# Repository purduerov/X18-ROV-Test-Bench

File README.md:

# X18 ROV Test Bench

Surface test-bench hardware for the Purdue ROV team (X18 vehicle generation):
carrier and power boards for topside validation without the vehicle in the water.

## Layout

- `MCU and Pi Board/` — MCU + Raspberry Pi carrier board
  (`mcu and pi board.kicad_sch` / `.kicad_pcb`, project-local `Libraries/`,
  `custom library.*`)
- `power/` — power distribution board (`power.kicad_sch` / `.kicad_pcb`,
  `power_symbols.*`, rail sheets such as `12-5`, `48-12`, `STM`)

## Tooling

- Designed in KiCad — open the `.kicad_pro` in each board folder.
- Fab/plot outputs (`outputs/`, `manufacturing/`, Gerbers), KiCad
  auto-backups (`*-backups/`), caches, and component source archives
  (`*.zip`) are git-ignored; regenerate them locally.

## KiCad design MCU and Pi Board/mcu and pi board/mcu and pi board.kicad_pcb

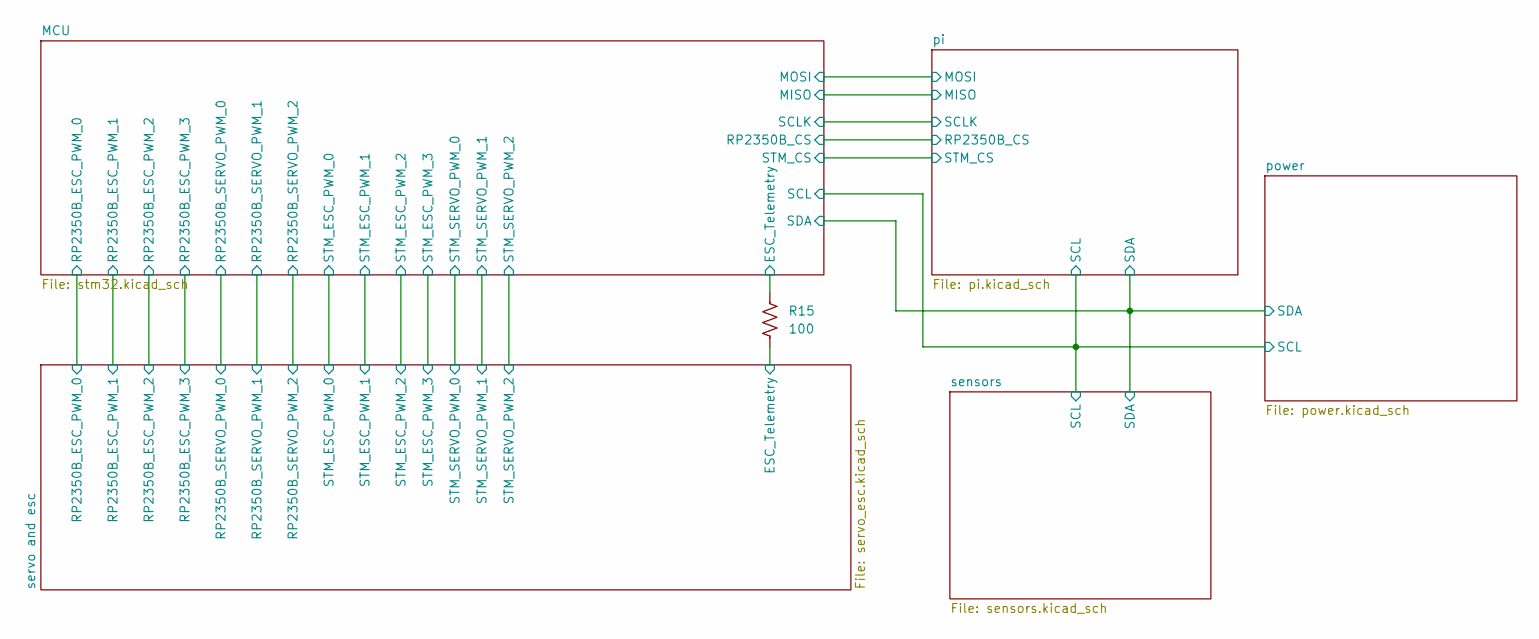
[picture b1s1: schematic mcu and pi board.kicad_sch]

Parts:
R15: 100; R_0603_1608Metric_Pad0.98x0.95mm_HandSolder

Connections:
/MCU/GPIO13: R15.1; also elsewhere on the board
/servo and esc/ESC_Telemetry: R15.2; also elsewhere on the board

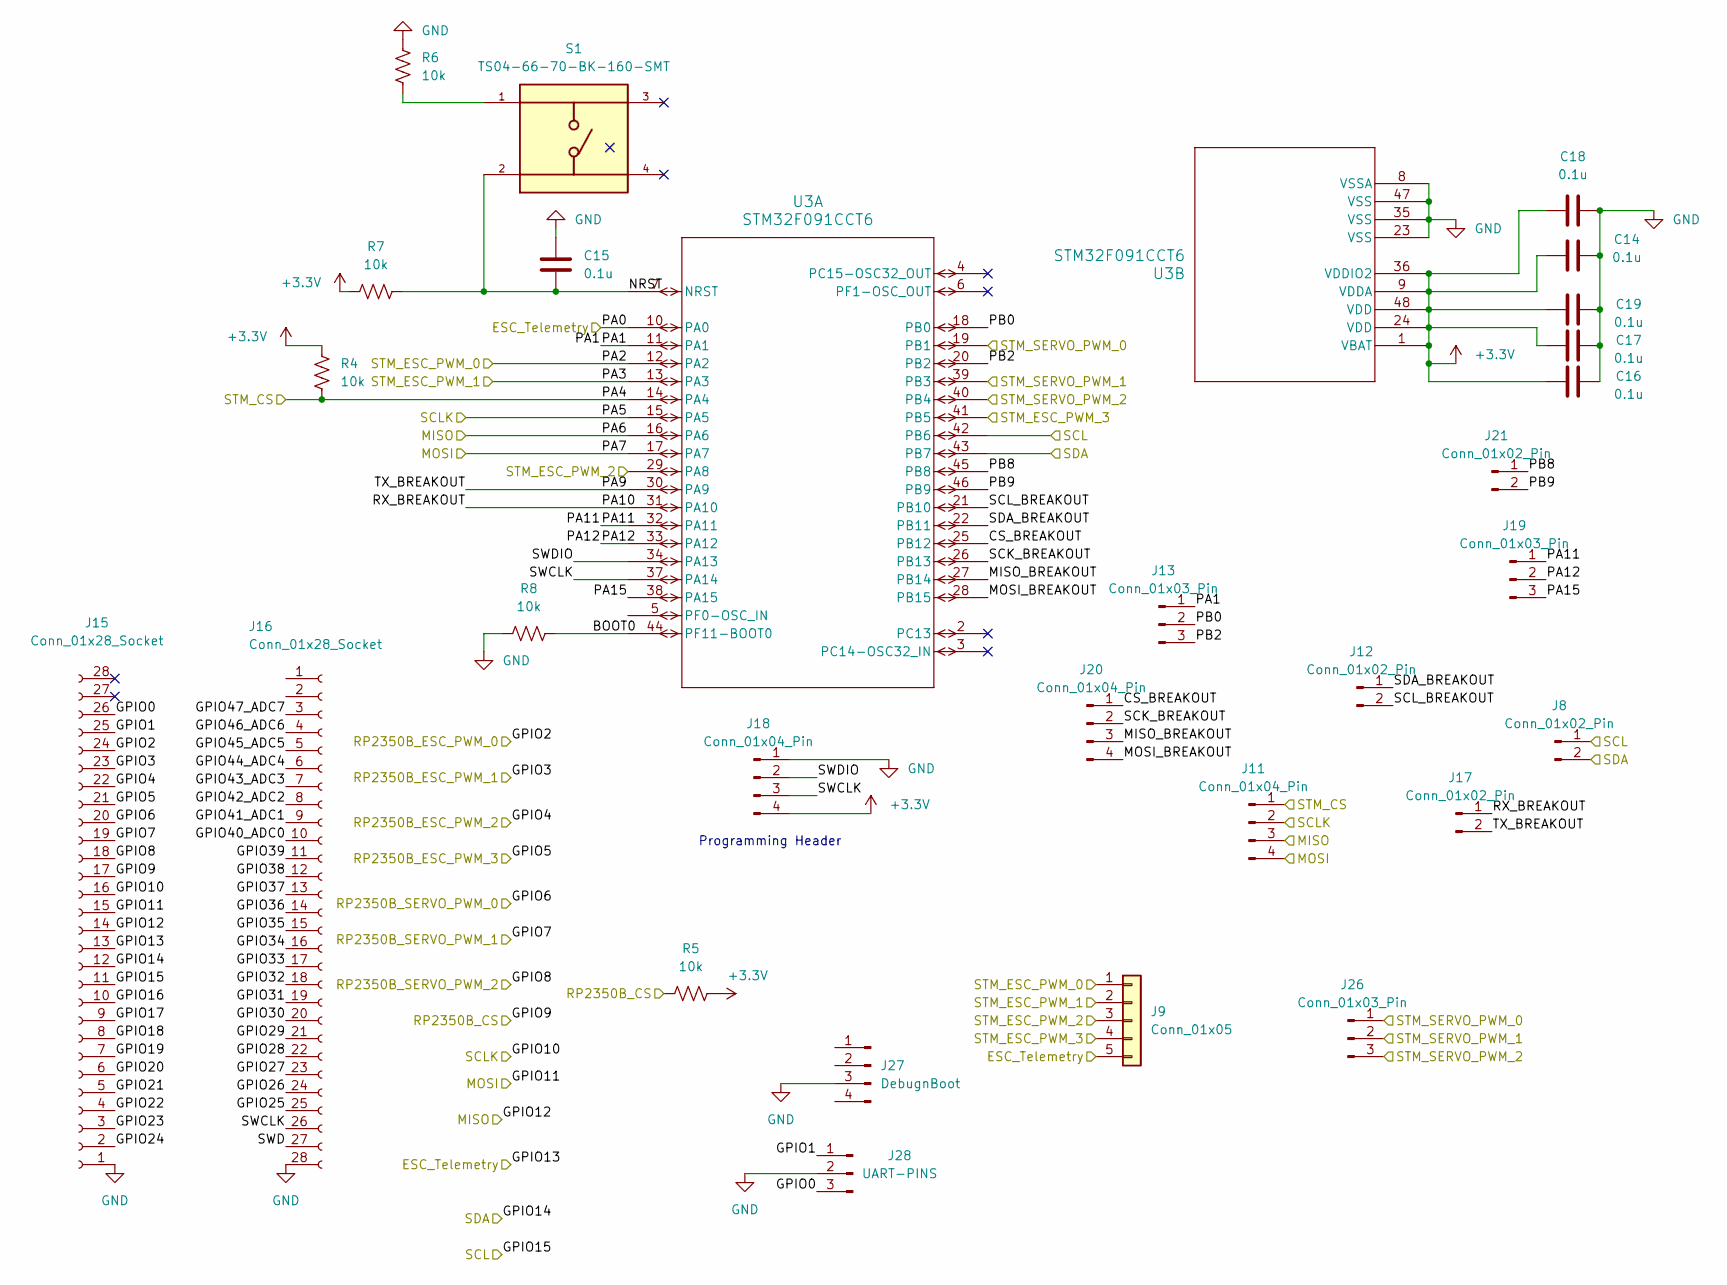
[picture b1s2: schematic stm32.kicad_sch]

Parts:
C14, C15, C16, C17, C18, C19: 0.1u; C_0603_1608Metric_Pad1.08x0.95mm_HandSolder; Voltage Rating 10V
J8, J12, J21: Conn_01x02_Pin; PinHeader_1x02_P2.54mm_Vertical
J9: Conn_01x05; PinSocket_1x05_P2.54mm_Vertical
J11, J18, J20: Conn_01x04_Pin; PinHeader_1x04_P2.54mm_Vertical
J13, J19: Conn_01x03_Pin; PinHeader_1x03_P2.54mm_Vertical
J15, J16: Conn_01x28_Socket; PinSocket_1x28_P2.54mm_Vertical
J17: Conn_01x02_Pin; PinSocket_1x02_P2.54mm_Vertical
J26: Conn_01x03_Pin; PinSocket_1x03_P2.54mm_Vertical
J27: DebugnBoot; PinHeader_1x04_P2.54mm_Vertical
J28: UART-PINS; PinHeader_1x03_P2.54mm_Vertical
R4, R5, R6, R7, R8: 10k; R_0603_1608Metric_Pad0.98x0.95mm_HandSolder
S1: TS04-66-70-BK-160-SMT; SW_TS04-66-70-BK-160-SMT; PARTREV 1.0
U3: STM32F091CCT6; LQFP48-7x7mm

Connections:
+3.3V: C14.1, C16.1, C17.1, C18.1, C19.1, J18.4, R4.1, R5.2, R7.1, U3.1 (VBAT), U3.9 (VDDA), U3.24 (VDD), U3.36 (VDDIO2), U3.48 (VDD); also elsewhere on the board
/MCU/BOOT0: R8.2, U3.44 (PF11-BOOT0)
/MCU/CS_BREAKOUT: J20.1, U3.25 (PB12)
/MCU/GPIO0: J15.26, J28.3
/MCU/GPIO1: J15.25, J28.1
/MCU/GPIO2: J15.24; also elsewhere on the board
/MCU/GPIO3: J15.23; also elsewhere on the board
/MCU/GPIO4: J15.22; also elsewhere on the board
/MCU/GPIO5: J15.21; also elsewhere on the board
/MCU/GPIO6: J15.20; also elsewhere on the board
/MCU/GPIO7: J15.19; also elsewhere on the board
/MCU/GPIO8: J15.18; also elsewhere on the board
/MCU/GPIO9: J15.17, R5.1; also elsewhere on the board
/MCU/GPIO10: J11.2, J15.16, U3.15 (PA5); also elsewhere on the board
/MCU/GPIO11: J11.4, J15.15, U3.17 (PA7); also elsewhere on the board
/MCU/GPIO12: J11.3, J15.14, U3.16 (PA6); also elsewhere on the board
/MCU/GPIO13: J9.5, J15.13, U3.10 (PA0); also elsewhere on the board
/MCU/GPIO14: J8.2, J15.12, U3.43 (PB7); also elsewhere on the board
/MCU/GPIO15: J8.1, J15.11, U3.42 (PB6); also elsewhere on the board
/MCU/GPIO16: J15.10
/MCU/GPIO17: J15.9
/MCU/GPIO18: J15.8
/MCU/GPIO19: J15.7
/MCU/GPIO20: J15.6
/MCU/GPIO21: J15.5
/MCU/GPIO22: J15.4
/MCU/GPIO23: J15.3
/MCU/GPIO24: J15.2
/MCU/GPIO25: J16.25
/MCU/GPIO26: J16.24
/MCU/GPIO27: J16.23
/MCU/GPIO28: J16.22
/MCU/GPIO29: J16.21
/MCU/GPIO30: J16.20
/MCU/GPIO31: J16.19
/MCU/GPIO32: J16.18
/MCU/GPIO33: J16.17
/MCU/GPIO34: J16.16
/MCU/GPIO35: J16.15
/MCU/GPIO36: J16.14
/MCU/GPIO37: J16.13
/MCU/GPIO38: J16.12
/MCU/GPIO39: J16.11
/MCU/GPIO40_ADC0: J16.10
/MCU/GPIO41_ADC1: J16.9
/MCU/GPIO42_ADC2: J16.8
/MCU/GPIO43_ADC3: J16.7
/MCU/GPIO44_ADC4: J16.6
/MCU/GPIO45_ADC5: J16.5
/MCU/GPIO46_ADC6: J16.4
/MCU/GPIO47_ADC7: J16.3
/MCU/MISO_BREAKOUT: J20.3, U3.27 (PB14)
/MCU/MOSI_BREAKOUT: J20.4, U3.28 (PB15)
/MCU/NRST: C15.2, R7.2, S1.2, U3.7 (NRST)
/MCU/PA1: J13.1, U3.11 (PA1)
/MCU/PA2: J9.1, U3.12 (PA2); also elsewhere on the board
/MCU/PA3: J9.2, U3.13 (PA3); also elsewhere on the board
/MCU/PA4: J11.1, R4.2, U3.14 (PA4); also elsewhere on the board
/MCU/PA9: J17.2, U3.30 (PA9)
/MCU/PA10: J17.1, U3.31 (PA10)
/MCU/PA11: J19.1, U3.32 (PA11)
/MCU/PA12: J19.2, U3.33 (PA12)
/MCU/PA15: J19.3, U3.38 (PA15)
/MCU/PB0: J13.2, U3.18 (PB0)
/MCU/PB2: J13.3, U3.20 (PB2)
/MCU/PB8: J21.1, U3.45 (PB8)
/MCU/PB9: J21.2, U3.46 (PB9)
/MCU/SCK_BREAKOUT: J20.2, U3.26 (PB13)
/MCU/SCL_BREAKOUT: J12.2, U3.21 (PB10)
/MCU/SDA_BREAKOUT: J12.1, U3.22 (PB11)
/MCU/STM_ESC_PWM_2: J9.3, U3.29 (PA8); also elsewhere on the board
/MCU/STM_ESC_PWM_3: J9.4, U3.41 (PB5); also elsewhere on the board
/MCU/STM_SERVO_PWM_0: J26.1, U3.19 (PB1); also elsewhere on the board
/MCU/STM_SERVO_PWM_1: J26.2, U3.39 (PB3); also elsewhere on the board
/MCU/STM_SERVO_PWM_2: J26.3, U3.40 (PB4); also elsewhere on the board
/MCU/SWCLK: J16.26
/MCU/SWCLK: J18.3, U3.37 (PA14)
/MCU/SWD: J16.27
/MCU/SWDIO: J18.2, U3.34 (PA13)
GND: C14.2, C15.1, C16.2, C17.2, C18.2, C19.2, J15.1, J16.28, J18.1, J27.3, J28.2, R6.2, R8.1, U3.8 (VSSA), U3.23 (VSS), U3.35 (VSS), U3.47 (VSS); also elsewhere on the board
unnamed: R6.1, S1.1

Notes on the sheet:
Programming Header

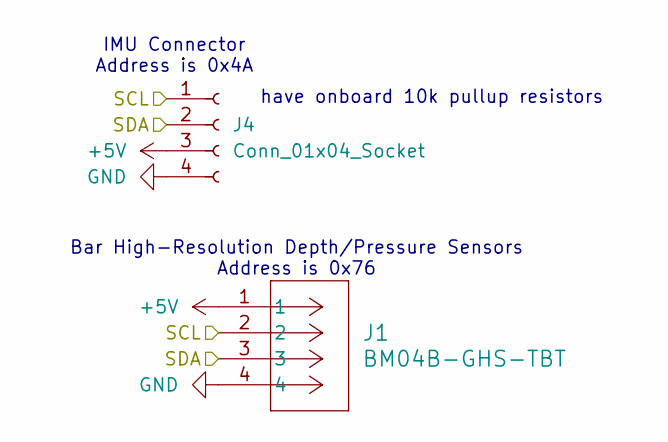
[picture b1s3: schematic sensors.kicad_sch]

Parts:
J1: BM04B-GHS-TBT; CONN_BM04B-GHS-TBT_JST
J4: Conn_01x04_Socket; JST_PH_S4B-PH-K_1x04_P2.00mm_Horizontal

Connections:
+5V: J1.1, J4.3; also elsewhere on the board
/MCU/GPIO14: J1.3, J4.2; also elsewhere on the board
/MCU/GPIO15: J1.2, J4.1; also elsewhere on the board
GND: J1.4, J4.4; also elsewhere on the board

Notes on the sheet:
Bar High-Resolution Depth/Pressure Sensors Address is 0x76
have onboard 10k pullup resistors
IMU Connector Address is 0x4A

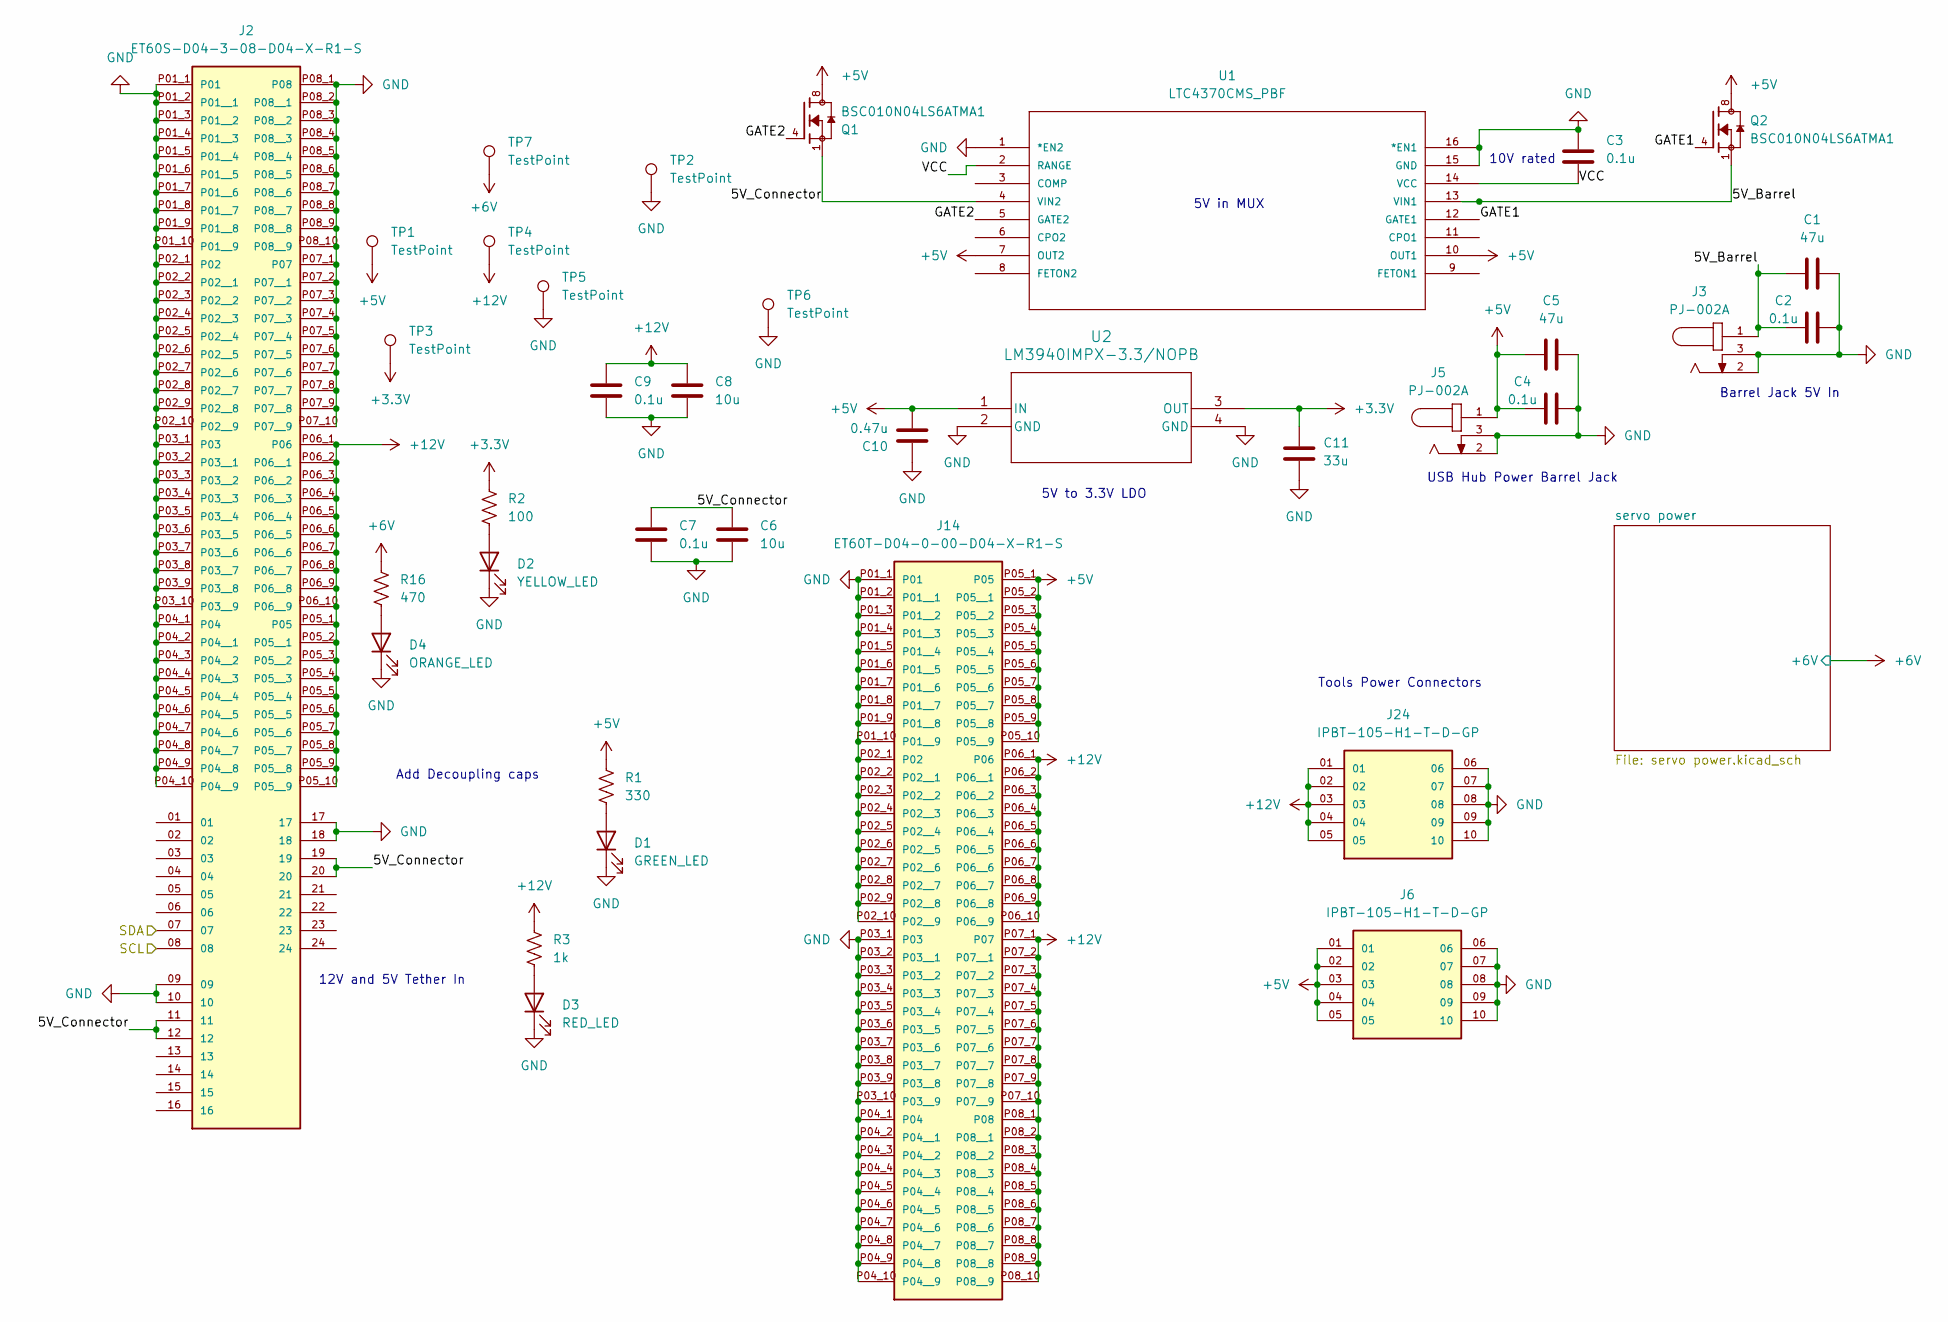
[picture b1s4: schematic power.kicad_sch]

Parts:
C1, C5: 47u; C_0805_2012Metric_Pad1.18x1.45mm_HandSolder; Voltage Rating 10V
C2, C3, C4, C7: 0.1u; C_0603_1608Metric_Pad1.08x0.95mm_HandSolder; Voltage Rating 10V
C6: 10u; C_0805_2012Metric_Pad1.18x1.45mm_HandSolder; Voltage Rating 10V
C8: 10u; C_0805_2012Metric_Pad1.18x1.45mm_HandSolder; Voltage Rating 25V
C9: 0.1u; C_0603_1608Metric_Pad1.08x0.95mm_HandSolder; Voltage Rating 25V
C10: 0.47u; C_0603_1608Metric_Pad1.08x0.95mm_HandSolder; Voltage Rating 10V
C11: 33u; C_0805_2012Metric_Pad1.18x1.45mm_HandSolder; Voltage Rating 10V
D1: GREEN_LED; LED_0805_2012Metric_Pad1.15x1.40mm_HandSolder
D2: YELLOW_LED; LED_0805_2012Metric_Pad1.15x1.40mm_HandSolder
D3: RED_LED; LED_0603_1608Metric_Pad1.05x0.95mm_HandSolder
D4: ORANGE_LED; LED_0603_1608Metric_Pad1.05x0.95mm_HandSolder
J2: ET60S-D04-3-08-D04-X-R1-S; SAMTEC_ET60S-D04-3-08-D04-X-R1-S; PARTREV G
J3, J5: PJ-002A; CUI_PJ-002A
J6, J24: IPBT-105-H1-T-D-GP; SAMTEC_IPBT-105-H1-T-D-GP; PARTREV R
J14: ET60T-D04-0-00-D04-X-R1-S; SAMTEC_ET60T-D04-0-00-D04-X-R1-S; PARTREV K
Q1, Q2: BSC010N04LS6ATMA1; TRANS_BSC010N04LS6ATMA1
R1: 330; R_0603_1608Metric_Pad0.98x0.95mm_HandSolder
R2: 100; R_0603_1608Metric_Pad0.98x0.95mm_HandSolder
R3: 1k; R_0603_1608Metric_Pad0.98x0.95mm_HandSolder
R16: 470; R_0603_1608Metric_Pad0.98x0.95mm_HandSolder
TP1, TP2, TP3, TP4, TP5, TP6, TP7: TestPoint; TestPoint_Pad_D4.0mm
U1: LTC4370CMS_PBF; MSOP-16_MS; MANUFACTURER_PART_NUMBER ltc4370cms#pbf
U2: LM3940IMPX-3.3/NOPB; MP04A

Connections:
+3.3V: C11.1, R2.1, TP3.1, U2.3 (OUT); also elsewhere on the board
+5V: C4.2, C5.1, C10.2, J5.1, J6.01, J6.02, J6.03, J6.04, J6.05, J14.P05_1 (P05), J14.P05_2 (P05__1), J14.P05_3 (P05__2), J14.P05_4 (P05__3), J14.P05_5 (P05__4), J14.P05_6 (P05__5), J14.P05_7 (P05__6), J14.P05_8 (P05__7), J14.P05_9 (P05__8), J14.P05_10 (P05__9), Q1.8, Q2.8, R1.1, TP1.1, U1.7 (OUT2), U1.10 (OUT1), U2.1 (IN); also elsewhere on the board
+6V: R16.1, TP7.1; also elsewhere on the board
+12V: C8.1, C9.1, J2.P05_1 (P05), J2.P05_2 (P05__1), J2.P05_3 (P05__2), J2.P05_4 (P05__3), J2.P05_5 (P05__4), J2.P05_6 (P05__5), J2.P05_7 (P05__6), J2.P05_8 (P05__7), J2.P05_9 (P05__8), J2.P05_10 (P05__9), J2.P06_1 (P06), J2.P06_2 (P06__1), J2.P06_3 (P06__2), J2.P06_4 (P06__3), J2.P06_5 (P06__4), J2.P06_6 (P06__5), J2.P06_7 (P06__6), J2.P06_8 (P06__7), J2.P06_9 (P06__8), J2.P06_10 (P06__9), J14.P06_1 (P06), J14.P06_2 (P06__1), J14.P06_3 (P06__2), J14.P06_4 (P06__3), J14.P06_5 (P06__4), J14.P06_6 (P06__5), J14.P06_7 (P06__6), J14.P06_8 (P06__7), J14.P06_9 (P06__8), J14.P06_10 (P06__9), J14.P07_1 (P07), J14.P07_2 (P07__1), J14.P07_3 (P07__2), J14.P07_4 (P07__3), J14.P07_5 (P07__4), J14.P07_6 (P07__5), J14.P07_7 (P07__6), J14.P07_8 (P07__7), J14.P07_9 (P07__8), J14.P07_10 (P07__9), J14.P08_1 (P08), J14.P08_2 (P08__1), J14.P08_3 (P08__2), J14.P08_4 (P08__3), J14.P08_5 (P08__4), J14.P08_6 (P08__5), J14.P08_7 (P08__6), J14.P08_8 (P08__7), J14.P08_9 (P08__8), J14.P08_10 (P08__9), J24.01, J24.02, J24.03, J24.04, J24.05, R3.1, TP4.1; also elsewhere on the board
/MCU/GPIO14: J2.07; also elsewhere on the board
/MCU/GPIO15: J2.08; also elsewhere on the board
/power/5V_Barrel: C1.1, C2.2, J3.1, Q2.1, U1.13 (VIN1)
/power/5V_Connector: C6.1, C7.1, J2.11, J2.12, J2.19, J2.20, Q1.1, U1.4 (VIN2)
/power/GATE1: Q2.4, U1.12 (GATE1)
/power/GATE2: Q1.4, U1.5 (GATE2)
/power/VCC: C3.2, U1.2 (RANGE), U1.14 (VCC)
GND: C1.2, C2.1, C3.1, C4.1, C5.2, C6.2, C7.2, C8.2, C9.2, C10.1, C11.2, D1.1 (K), D2.1 (K), D3.1 (K), D4.1 (K), J2.09, J2.10, J2.17, J2.18, J2.P01_1 (P01), J2.P01_2 (P01__1), J2.P01_3 (P01__2), J2.P01_4 (P01__3), J2.P01_5 (P01__4), J2.P01_6 (P01__5), J2.P01_7 (P01__6), J2.P01_8 (P01__7), J2.P01_9 (P01__8), J2.P01_10 (P01__9), J2.P02_1 (P02), J2.P02_2 (P02__1), J2.P02_3 (P02__2), J2.P02_4 (P02__3), J2.P02_5 (P02__4), J2.P02_6 (P02__5), J2.P02_7 (P02__6), J2.P02_8 (P02__7), J2.P02_9 (P02__8), J2.P02_10 (P02__9), J2.P03_1 (P03), J2.P03_2 (P03__1), J2.P03_3 (P03__2), J2.P03_4 (P03__3), J2.P03_5 (P03__4), J2.P03_6 (P03__5), J2.P03_7 (P03__6), J2.P03_8 (P03__7), J2.P03_9 (P03__8), J2.P03_10 (P03__9), J2.P04_1 (P04), J2.P04_2 (P04__1), J2.P04_3 (P04__2), J2.P04_4 (P04__3), J2.P04_5 (P04__4), J2.P04_6 (P04__5), J2.P04_7 (P04__6), J2.P04_8 (P04__7), J2.P04_9 (P04__8), J2.P04_10 (P04__9), J2.P07_1 (P07), J2.P07_2 (P07__1), J2.P07_3 (P07__2), J2.P07_4 (P07__3), J2.P07_5 (P07__4), J2.P07_6 (P07__5), J2.P07_7 (P07__6), J2.P07_8 (P07__7), J2.P07_9 (P07__8), J2.P07_10 (P07__9), J2.P08_1 (P08), J2.P08_2 (P08__1), J2.P08_3 (P08__2), J2.P08_4 (P08__3), J2.P08_5 (P08__4), J2.P08_6 (P08__5), J2.P08_7 (P08__6), J2.P08_8 (P08__7), J2.P08_9 (P08__8), J2.P08_10 (P08__9), J3.2, J3.3, J5.2, J5.3, J6.06, J6.07, J6.08, J6.09, J6.10, J14.P01_1 (P01), J14.P01_2 (P01__1), J14.P01_3 (P01__2), J14.P01_4 (P01__3), J14.P01_5 (P01__4), J14.P01_6 (P01__5), J14.P01_7 (P01__6), J14.P01_8 (P01__7), J14.P01_9 (P01__8), J14.P01_10 (P01__9), J14.P02_1 (P02), J14.P02_2 (P02__1), J14.P02_3 (P02__2), J14.P02_4 (P02__3), J14.P02_5 (P02__4), J14.P02_6 (P02__5), J14.P02_7 (P02__6), J14.P02_8 (P02__7), J14.P02_9 (P02__8), J14.P02_10 (P02__9), J14.P03_1 (P03), J14.P03_2 (P03__1), J14.P03_3 (P03__2), J14.P03_4 (P03__3), J14.P03_5 (P03__4), J14.P03_6 (P03__5), J14.P03_7 (P03__6), J14.P03_8 (P03__7), J14.P03_9 (P03__8), J14.P03_10 (P03__9), J14.P04_1 (P04), J14.P04_2 (P04__1), J14.P04_3 (P04__2), J14.P04_4 (P04__3), J14.P04_5 (P04__4), J14.P04_6 (P04__5), J14.P04_7 (P04__6), J14.P04_8 (P04__7), J14.P04_9 (P04__8), J14.P04_10 (P04__9), J24.06, J24.07, J24.08, J24.09, J24.10, TP2.1, TP5.1, TP6.1, U1.1 (*EN2), U1.15 (GND), U1.16 (*EN1), U2.2 (GND), U2.4 (GND); also elsewhere on the board
unnamed: D1.2 (A), R1.2
unnamed: D2.2 (A), R2.2
unnamed: D3.2 (A), R3.2
unnamed: D4.2 (A), R16.2

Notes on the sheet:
USB Hub Power Barrel Jack
Barrel Jack 5V In
12V and 5V Tether In
10V rated
Tools Power Connectors
Add Decoupling caps
5V to 3.3V LDO
5V in MUX

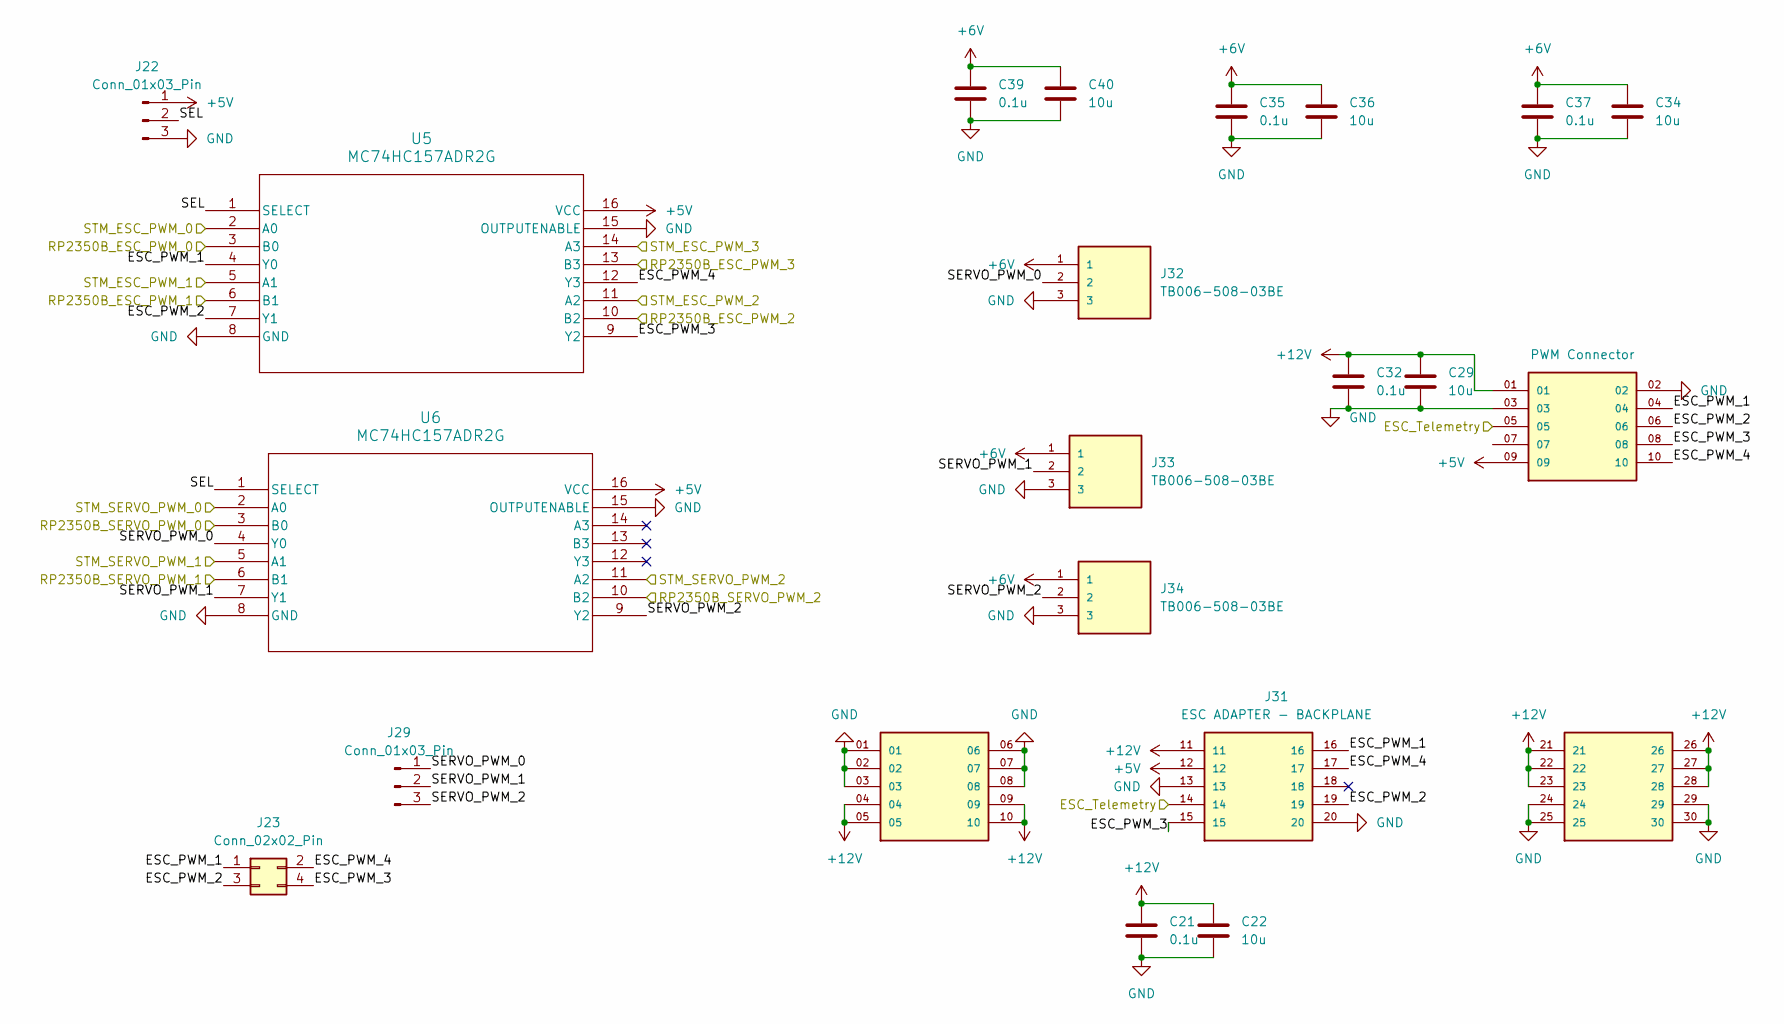
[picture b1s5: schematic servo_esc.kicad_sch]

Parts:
C21, C32, C35, C37, C39: 0.1u; C_0603_1608Metric_Pad1.08x0.95mm_HandSolder; Voltage Rating 25V
C22, C29, C34, C36, C40: 10u; C_0805_2012Metric_Pad1.18x1.45mm_HandSolder; Voltage Rating 25V
J22: Conn_01x03_Pin; PinHeader_1x03_P2.54mm_Vertical
J23: Conn_02x02_Pin; PinSocket_2x02_P2.54mm_Vertical
J29: Conn_01x03_Pin; PinSocket_1x03_P2.54mm_Vertical
J30: PWM Connector; PWM, 12V, GND JST Connector; PARTREV R
J31: ESC ADAPTER - BACKPLANE; ESC Adapter - Backplane; PARTREV R
J32, J33, J34: TB006-508-03BE; CUI_TB006-508-03BE
U5, U6: MC74HC157ADR2G; SOIC-16_ONS

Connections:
+5V: J22.1, J30.09, J31.12, U5.16 (VCC), U6.16 (VCC); also elsewhere on the board
+6V: C34.1, C35.1, C36.1, C37.1, C39.1, C40.1, J32.1, J33.1, J34.1; also elsewhere on the board
+12V: C21.1, C22.1, C29.1, C32.1, J30.01, J31.04, J31.05, J31.09, J31.10, J31.11, J31.21, J31.22, J31.23, J31.26, J31.27, J31.28; also elsewhere on the board
/MCU/GPIO2: U5.3 (B0); also elsewhere on the board
/MCU/GPIO3: U5.6 (B1); also elsewhere on the board
/MCU/GPIO4: U5.10 (B2); also elsewhere on the board
/MCU/GPIO5: U5.13 (B3); also elsewhere on the board
/MCU/GPIO6: U6.3 (B0); also elsewhere on the board
/MCU/GPIO7: U6.6 (B1); also elsewhere on the board
/MCU/GPIO8: U6.10 (B2); also elsewhere on the board
/MCU/PA2: U5.2 (A0); also elsewhere on the board
/MCU/PA3: U5.5 (A1); also elsewhere on the board
/MCU/STM_ESC_PWM_2: U5.11 (A2); also elsewhere on the board
/MCU/STM_ESC_PWM_3: U5.14 (A3); also elsewhere on the board
/MCU/STM_SERVO_PWM_0: U6.2 (A0); also elsewhere on the board
/MCU/STM_SERVO_PWM_1: U6.5 (A1); also elsewhere on the board
/MCU/STM_SERVO_PWM_2: U6.11 (A2); also elsewhere on the board
/servo and esc/ESC_PWM_1: J23.1, J30.04, J31.16, U5.4 (Y0)
/servo and esc/ESC_PWM_2: J23.3, J30.06, J31.19, U5.7 (Y1)
/servo and esc/ESC_PWM_3: J23.4, J30.08, J31.15, U5.9 (Y2)
/servo and esc/ESC_PWM_4: J23.2, J30.10, J31.17, U5.12 (Y3)
/servo and esc/ESC_Telemetry: J30.05, J31.14; also elsewhere on the board
/servo and esc/SEL: J22.2, U5.1 (SELECT), U6.1 (SELECT)
/servo and esc/SERVO_PWM_0: J29.1, J32.2, U6.4 (Y0)
/servo and esc/SERVO_PWM_1: J29.2, J33.2, U6.7 (Y1)
/servo and esc/SERVO_PWM_2: J29.3, J34.2, U6.9 (Y2)
GND: C21.2, C22.2, C29.2, C32.2, C34.2, C35.2, C36.2, C37.2, C39.2, C40.2, J22.3, J30.02, J30.03, J31.01, J31.02, J31.03, J31.06, J31.07, J31.08, J31.13, J31.20, J31.24, J31.25, J31.29, J31.30, J32.3, J33.3, J34.3, U5.8 (GND), U5.15 (OUTPUTENABLE), U6.8 (GND), U6.15 (OUTPUTENABLE); also elsewhere on the board

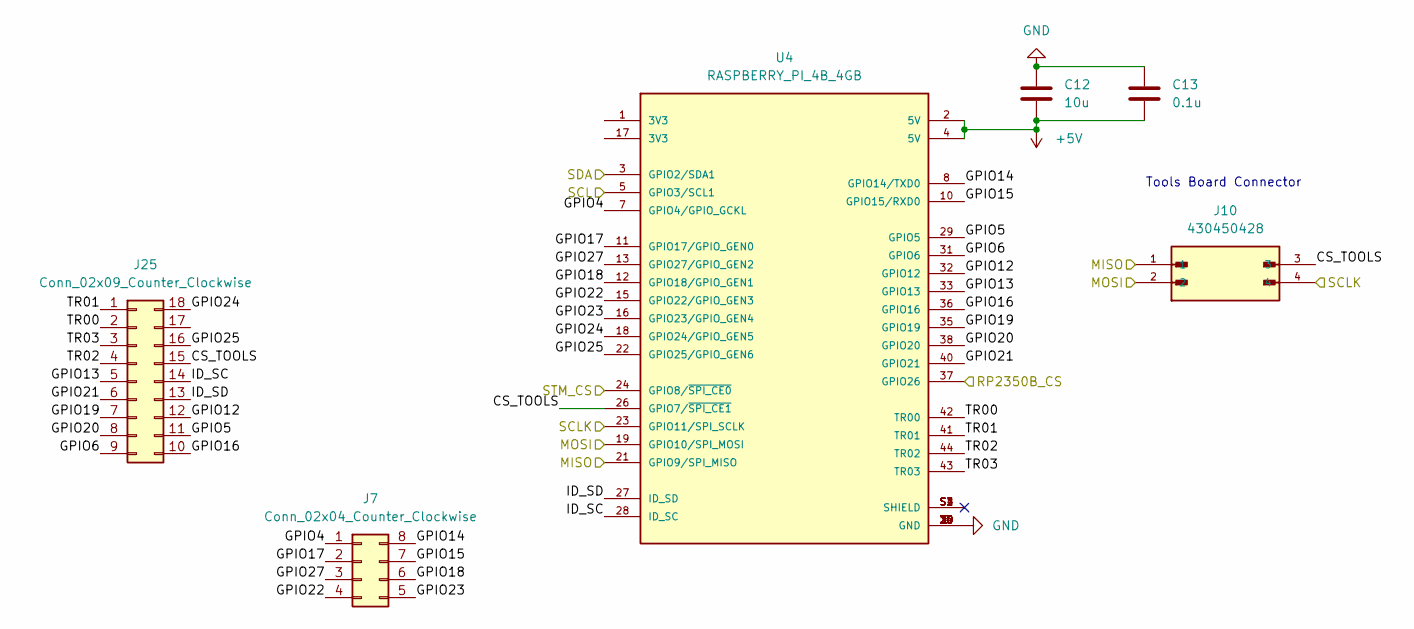
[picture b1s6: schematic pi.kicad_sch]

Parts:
C12: 10u; C_0603_1608Metric_Pad1.08x0.95mm_HandSolder; Voltage Rating 10V
C13: 0.1u; C_0603_1608Metric_Pad1.08x0.95mm_HandSolder; Voltage Rating 10V
J7: Conn_02x04_Counter_Clockwise; PinHeader_2x04_P2.54mm_Vertical
J10: 430450428; MOLEX_430450428; PARTREV G1
J25: Conn_02x09_Counter_Clockwise; PinHeader_2x09_P2.54mm_Vertical
U4: RASPBERRY_PI_4B_4GB; MODULE_RASPBERRY_PI_4B_4GB; PARTREV 4

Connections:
+5V: C12.2, C13.2, U4.2 (5V), U4.4 (5V); also elsewhere on the board
/MCU/GPIO9: U4.37 (GPIO26); also elsewhere on the board
/MCU/GPIO10: J10.4, U4.23 (GPIO11/SPI_SCLK); also elsewhere on the board
/MCU/GPIO11: J10.2, U4.19 (GPIO10/SPI_MOSI); also elsewhere on the board
/MCU/GPIO12: J10.1, U4.21 (GPIO9/SPI_MISO); also elsewhere on the board
/MCU/GPIO14: U4.3 (GPIO2/SDA1); also elsewhere on the board
/MCU/GPIO15: U4.5 (GPIO3/SCL1); also elsewhere on the board
/MCU/PA4: U4.24 (GPIO8/~SPI_CE0); also elsewhere on the board
/pi/CS_TOOLS: J10.3, J25.15, U4.26 (GPIO7/~SPI_CE1)
/pi/GPIO4: J7.1, U4.7 (GPIO4/GPIO_GCKL)
/pi/GPIO5: J25.11, U4.29 (GPIO5)
/pi/GPIO6: J25.9, U4.31 (GPIO6)
/pi/GPIO12: J25.12, U4.32 (GPIO12)
/pi/GPIO13: J25.5, U4.33 (GPIO13)
/pi/GPIO14: J7.8, U4.8 (GPIO14/TXD0)
/pi/GPIO15: J7.7, U4.10 (GPIO15/RXD0)
/pi/GPIO16: J25.10, U4.36 (GPIO16)
/pi/GPIO17: J7.2, U4.11 (GPIO17/GPIO_GEN0)
/pi/GPIO18: J7.6, U4.12 (GPIO18/GPIO_GEN1)
/pi/GPIO19: J25.7, U4.35 (GPIO19)
/pi/GPIO20: J25.8, U4.38 (GPIO20)
/pi/GPIO21: J25.6, U4.40 (GPIO21)
/pi/GPIO22: J7.4, U4.15 (GPIO22/GPIO_GEN3)
/pi/GPIO23: J7.5, U4.16 (GPIO23/GPIO_GEN4)
/pi/GPIO24: J25.18, U4.18 (GPIO24/GPIO_GEN5)
/pi/GPIO25: J25.16, U4.22 (GPIO25/GPIO_GEN6)
/pi/GPIO27: J7.3, U4.13 (GPIO27/GPIO_GEN2)
/pi/ID_SC: J25.14, U4.28 (ID_SC)
/pi/ID_SD: J25.13, U4.27 (ID_SD)
/pi/TR00: J25.2, U4.42 (TR00)
/pi/TR01: J25.1, U4.41 (TR01)
/pi/TR02: J25.4, U4.44 (TR02)
/pi/TR03: J25.3, U4.43 (TR03)
GND: C12.1, C13.1, U4.6 (GND), U4.9 (GND), U4.14 (GND), U4.20 (GND), U4.25 (GND), U4.30 (GND), U4.34 (GND), U4.39 (GND); also elsewhere on the board

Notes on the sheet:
Tools Board Connector

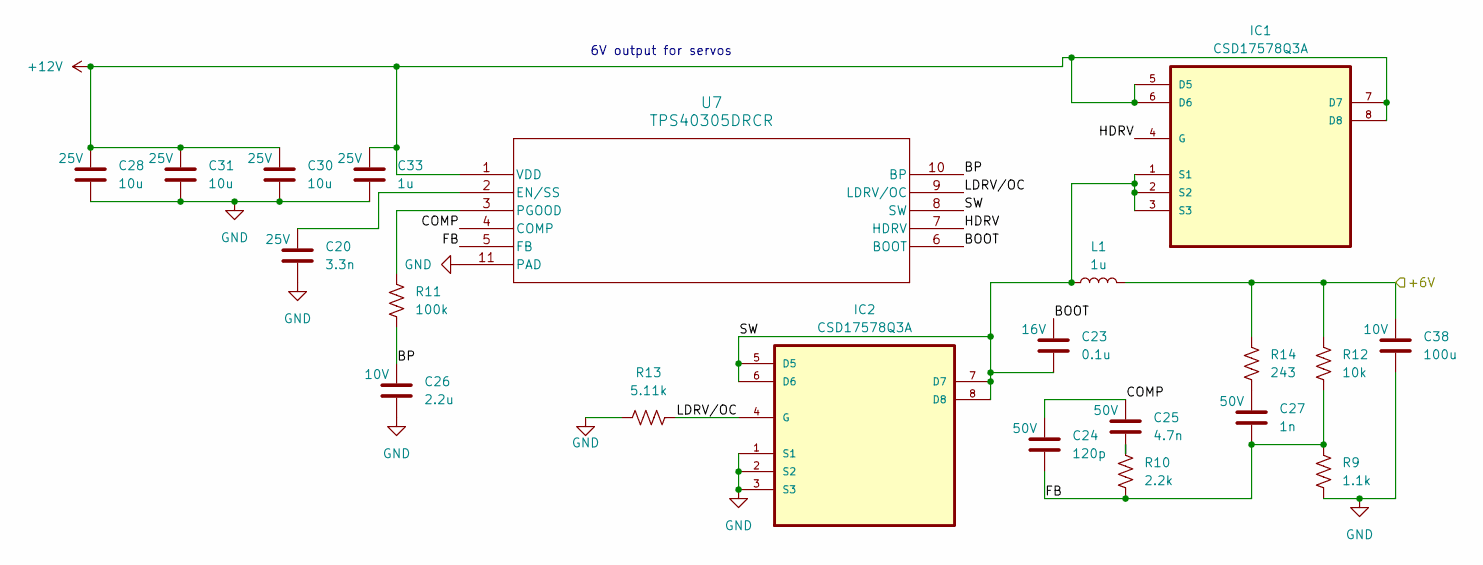
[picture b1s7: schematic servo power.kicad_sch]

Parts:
C20: 3.3n; C_0805_2012Metric_Pad1.18x1.45mm_HandSolder; Voltage Rating 25V
C23: 0.1u; C_0603_1608Metric_Pad1.08x0.95mm_HandSolder; Voltage Rating 16V
C24: 120p; C_0603_1608Metric_Pad1.08x0.95mm_HandSolder; Voltage Rating 50V
C25: 4.7n; C_0805_2012Metric_Pad1.18x1.45mm_HandSolder; Voltage Rating 50V
C26: 2.2u; C_0603_1608Metric_Pad1.08x0.95mm_HandSolder; Voltage Rating 10V
C27: 1n; C_0603_1608Metric_Pad1.08x0.95mm_HandSolder; Voltage Rating 50V
C28, C30, C31: 10u; C_0805_2012Metric_Pad1.18x1.45mm_HandSolder; Voltage Rating 25V
C33: 1u; C_0603_1608Metric_Pad1.08x0.95mm_HandSolder; Voltage Rating 25V
C38: 100u; C_1206_3216Metric_Pad1.33x1.80mm_HandSolder; Voltage Rating 10V
IC1, IC2: CSD17578Q3A; TRANS_CSD18543Q3A
L1: 1u; IND_XAL6030-102MEC
R9: 1.1k; R_0603_1608Metric_Pad0.98x0.95mm_HandSolder
R10: 2.2k; R_0603_1608Metric_Pad0.98x0.95mm_HandSolder
R11: 100k; R_0603_1608Metric_Pad0.98x0.95mm_HandSolder
R12: 10k; R_0603_1608Metric_Pad0.98x0.95mm_HandSolder
R13: 5.11k; R_0603_1608Metric_Pad0.98x0.95mm_HandSolder
R14: 243; R_0603_1608Metric_Pad0.98x0.95mm_HandSolder
U7: TPS40305DRCR; DRC10_2P4X1P65

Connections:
+6V: C38.1, L1.2, R12.1, R14.1; also elsewhere on the board
+12V: C28.1, C30.1, C31.1, C33.1, IC1.5 (D5), IC1.6 (D6), IC1.7 (D7), IC1.8 (D8), U7.1 (VDD); also elsewhere on the board
/power/servo power/BOOT: C23.1, U7.6 (BOOT)
/power/servo power/BP: C26.1, R11.2, U7.10 (BP)
/power/servo power/COMP: C24.1, C25.1, U7.4 (COMP)
/power/servo power/FB: C24.2, C27.2, R9.1, R10.2, R12.2, U7.5 (FB)
/power/servo power/HDRV: IC1.4 (G), U7.7 (HDRV)
/power/servo power/LDRV/OC: IC2.4 (G), R13.2, U7.9 (LDRV/OC)
/power/servo power/SW: C23.2, IC1.1 (S1), IC1.2 (S2), IC1.3 (S3), IC2.5 (D5), IC2.6 (D6), IC2.7 (D7), IC2.8 (D8), L1.1, U7.8 (SW)
GND: C20.2, C26.2, C28.2, C30.2, C31.2, C33.2, C38.2, IC2.1 (S1), IC2.2 (S2), IC2.3 (S3), R9.2, R13.1, U7.11 (PAD); also elsewhere on the board
unnamed: C25.2, R10.1
unnamed: C27.1, R14.2
unnamed: C20.1, U7.2 (EN/SS)
unnamed: R11.1, U7.3 (PGOOD)

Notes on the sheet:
6V output for servos

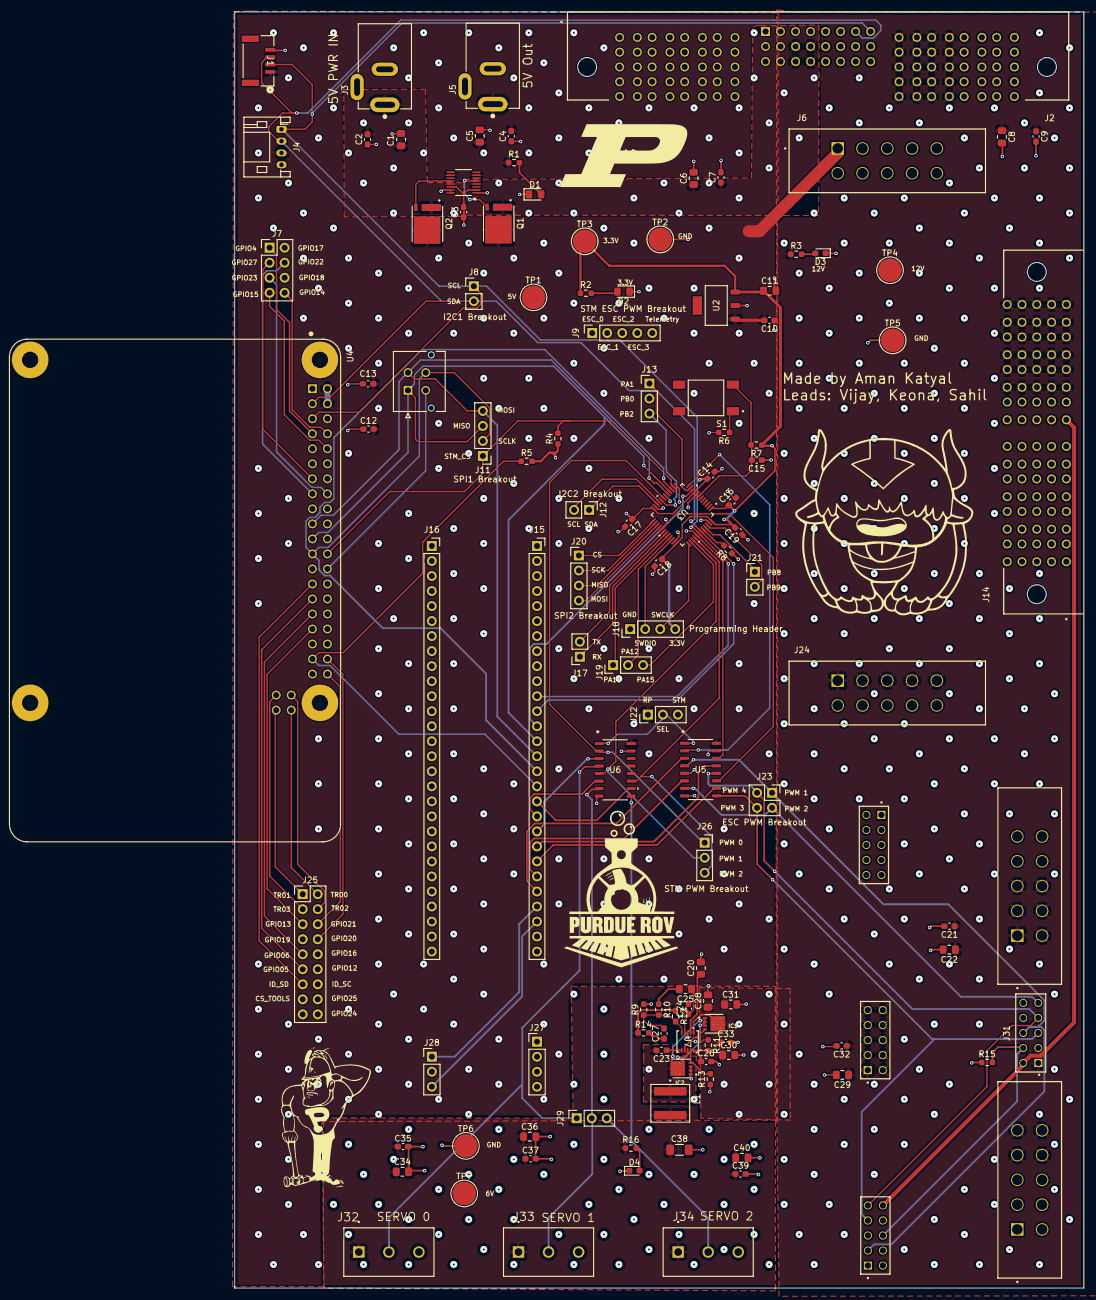
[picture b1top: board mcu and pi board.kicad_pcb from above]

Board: 4 copper layers, 143.6 x 215.8 mm, 114 parts (0 on the bottom side), 104 nets.
